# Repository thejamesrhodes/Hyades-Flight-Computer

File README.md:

---

# Hyades Flight Computer

Custom STM32H743 flight computer and GNC software for a roll-rate-stabilised high-power rocket.

*This is an engineering project, not a product. The safety case, regulatory compliance, and airworthiness of any vehicle built from this material are the builder's sole responsibility.*

The project is designed to:
- Provide a modular active roll-rate damping system suitable for a wide range of high-power rockets.
- Improve flight data quality by reducing excessive vehicle roll.
- Improve parachute deployment reliability by limiting roll-induced line twist.
- Provide a reusable avionics platform for future guidance, navigation and control research.
- Maintain compliance with applicable rocketry regulations through both hardware and software design decisions.
- Release all hardware, firmware and simulation tools as open source.

**Control scope.** The flight controller closes a loop on roll *rate*, not roll *angle*. It damps rate transients and cancels the standing roll moment produced by build asymmetry. It holds no commanded heading and has no outer attitude loop. Roll-angle hold and full three-axis attitude control are planned work and are not implemented.

This repository contains the hardware design, embedded software, simulation models, and analysis tools used during development.

---

## Specification

| Parameter | Specification |
|-----------|---------------|
| Purpose | Active roll stabilisation for mid- and high-power rockets |
| Flight Computer | STM32H743 ARM Cortex-M7 |
| Control Surfaces | Four independently actuated canards |
| Control System | Proportional roll-rate damper, dynamic-pressure gain scheduled, with a slow bounded trim path for bias rejection |
| Control Scope | Roll rate damping and bias rejection. No attitude loop |
| Interfaces | I²C, UART and 6× PWM outputs |
| Data | On-board logging with optional telemetry |
| Simulation | MATLAB, Simulink, 6DOF modelling and Monte Carlo analysis |
| Architecture | Modular flight computer, sensor board and power distribution board |
| Design Goals | Low mass, modular, reliable and adaptable |
| License | Apache 2.0 |

---

## Project Progress

| Feature                         | Status |
|---------------------------------|:------:|
| Flight Computer Design          | Complete |
| Flight Computer Testing         | In Progress |
| Flight Software                 | In Progress |
| Flight Hardware Design          | In Progress |
| Flight Hardware Testing         | In Progress |
| Simulink Roll Model             | Complete |
| Simulink 6DOF Model             | Complete |
| MATLAB Monte Carlo Analysis     | Complete |
| System Integration              | Not Started |
| HITL Testing                    | Not Started |
| Flight Testing                  | Not Started |

---

## Repository Structure

```text
Hyades-Flight-Computer
│
├── Documentation/
│   └── Images/
├── Firmware/
│   └── STM32IDE/
├── Hardware/
│   ├── 29mm Rocket/
│   ├── Avionics Bay/
│   ├── Canards/
│   ├── Fin Can/
│   └── PCB Designs/
└── Simulation/
    ├── Buck Regulator SPICE Simulation/
    ├── Canard Sizing/
    ├── HSE Clock SPICE Simulation/
    └── Matlab Roll Tuning/
```

---

## Flight Computer Design

The main PCB, containing all the computation and data gathering.

<p align="center"><i>Rev 0.2 render; rev 0.3 layout in progress.</i>
</p>

The PDB board, provides power and distributes PWM signals to the servos, as well as providing a clean 3V3 to the sensor board.

0 Ohm Series Termination vs 47 Ohm Series Termination for the 24 MHz HSE Oscillator, unnecessary? Yes, but a good opportunity to learn SPICE Simulations, plus it looks cool.
Below the schematic that the simulations were derived from.

---

## Flight Computer Testing

The second hardware iteration of the flight computer. The first failed due to many oversights and lack of basic knowledge.
On this version, the MCU boots and runs, USB and PDB works completely. An incorrectly wired CS pin has caused a bus fault where the I2C bus thinks its SPI and so fails to communicate. Future redesign to address this and a number of other design/architecture level issues is in progress, enabled by kind sponsorship from JLCPCB. Also seen is the Sheppard PCB design for my research project, which served a dual purpose in allowing me to validate the layout and connections for all the critical components for the next iteration, such as the ICM-42688P IMU and STM32H743 MCU and controlled impedance USB-HS routing for high data rate logging.

After some more testing, I have realised that the supposed ICM-42688-P's are actually QMI8658A IMU, substituted as a fake version of the target gyros (cross referenced WHO_AM_I 0x05, rev 0x7C, address 0x6B), after rewriting some of the code I got them working, allowing for a breakout board/bodge to be avoided. After collecting 2+ hours of data running at 16 g, 2048 dps, 224.2~ Hz ODR over I2C at 400kHz, I computed allan variance and then fitted a white-noise + Gauss-Markov + random-walk model to it (GMWM) with the rate-quantisation component computed separately under PQN model assumptions.

This is beneficial as the state estimator (IEKF) requires a model of the sensors noise to optimally estimate the current pose and to make its covariance trustworthy, which fault detection partly relies on. See [Quantisation Research Project](https://github.com/thejamesrhodes/IMU-Quantisation-research-project) for my related work on this topic.

---

## Flight Hardware Design

The built airframe, assembled and with the front avionics section separated from the booster.

CAD full assembly, an earlier render with the front section and nose cone missing.

Spinning Rear Fin Can designed to avoid the roll reversal phenomenon where upstream control surfaces tip vortices interact with the downstream fixed fins, causing a difficult to predict moment in the opposite direction.

Front avionics assembly, WIP.

---

## Flight Hardware Testing

%words

---

## Flight Software

%words

---

# Simulation

---

## Roll Control Architecture

The loop closes on roll rate, along two paths.

**Damping** is proportional and gain scheduled on dynamic pressure, `Kp = c / q_e`. The 1/q schedule holds the open-loop crossover constant across the envelope.

**Trim** is a slow bounded integrator that cancels the standing roll moment `Cl_0` from fin cant and build asymmetry. It is kept out of the damper because the deflection that cancels a standing bias, `-Cl_0 / Cl_delta`, is independent of q and V - one fixed deflection works everywhere, so it can be learned slowly and stay clear of the loop dynamics. Four gates bound it: bandwidth, a dead zone subtracted from the integrator input, a saturation freeze, and a clamp with a rate limit. It accepts an external `Cl_0` estimate, so a future MEKF can supply the value directly.

Putting integral action in the damper instead produces a limit cycle against the servo dead zone. That dead zone sits inside the servo's own position loop, so command-side compensation does not reach it; dither on the command does. Flown at 1.5x the modelled dead zone, 125 Hz.

**Open items.** The trim saturation gate tests the pre-dither command while the travel clamp acts post-dither, so it can miss a saturation event within one dither amplitude of the stop. The dither frequency also needs checking against the servo's maximum frame rate.

---

## Simulink Roll Model

%words

---

## Simulink 6DOF Model

%words

---

## MATLAB Monte Carlo Analysis

400 dispersed runs per design point. Aerodynamic coefficients, vehicle properties, actuator parameters and the disturbance bias are sampled per run. The controller's dynamic-pressure estimate is drawn about the sampled truth rather than the nominal, so scheduling error compounds with aerodynamic dispersion instead of cancelling against it.

| Metric | Definition |
|---|---|
| `rms_err` | RMS of (p - ref) over the steady tail |
| `bias` | mean(p) - ref over the tail |
| `ripple_pp` | max(p) - min(p) over the tail; limit-cycle amplitude |
| `activity` | RMS surface rate; catches stick-slip |
| `growth` | RMS of the last half of the tail over the first half; the stability test |
| `travel_peak` / `travel_steady` | Travel used over the whole run / over the tail |

Dither amplitude was swept over four campaigns at matched dispersion. Limit-cycle amplitude falls sharply at the flown setting with no rise in surface activity; the cost shows up as a small steady rate bias.

<!-- FIGURE SLOT A: settling-time and rate-error distributions, regenerated against
     the current canard geometry and the flown gainset. -->

<!-- FIGURE SLOT B: parameter-vs-outcome correlation structure, regenerated. -->

---

## MATLAB Gain Optimisation

`c` is set analytically from a 4 Hz crossover target; the numerical work confirms the margins near it survive parameter uncertainty rather than searching for an optimum. Margins come from the open-loop frequency response with the transport delay treated exactly, evaluated over paired (q, V) flight conditions spanning q = 2-40 kPa, with independent +/-30% on `Cl_delta` and `Cl_p`, accepted at phase margin >= 35 deg, gain margin >= 6 dB and peak sensitivity <= 2.0 at the worst corner. Constants are read from the parameter file rather than restated here.

A separate grid search over `c` and the trim parameters scores candidates on settling time, hang-off, limit-cycle amplitude and actuator demand, using the Monte Carlo campaign at each point.

`Ti` applies only to the legacy PI mode kept for A/B comparison.

<!-- FIGURE SLOT C: stability-margin and failure-probability maps over c, regenerated
     against the current canard. The previously published heatmaps are from the legacy
     PI controller and the earlier canard geometry. -->

---

## System Integration

%words

---

## HITL Testing

%words

---

## Flight Testing

%words

---

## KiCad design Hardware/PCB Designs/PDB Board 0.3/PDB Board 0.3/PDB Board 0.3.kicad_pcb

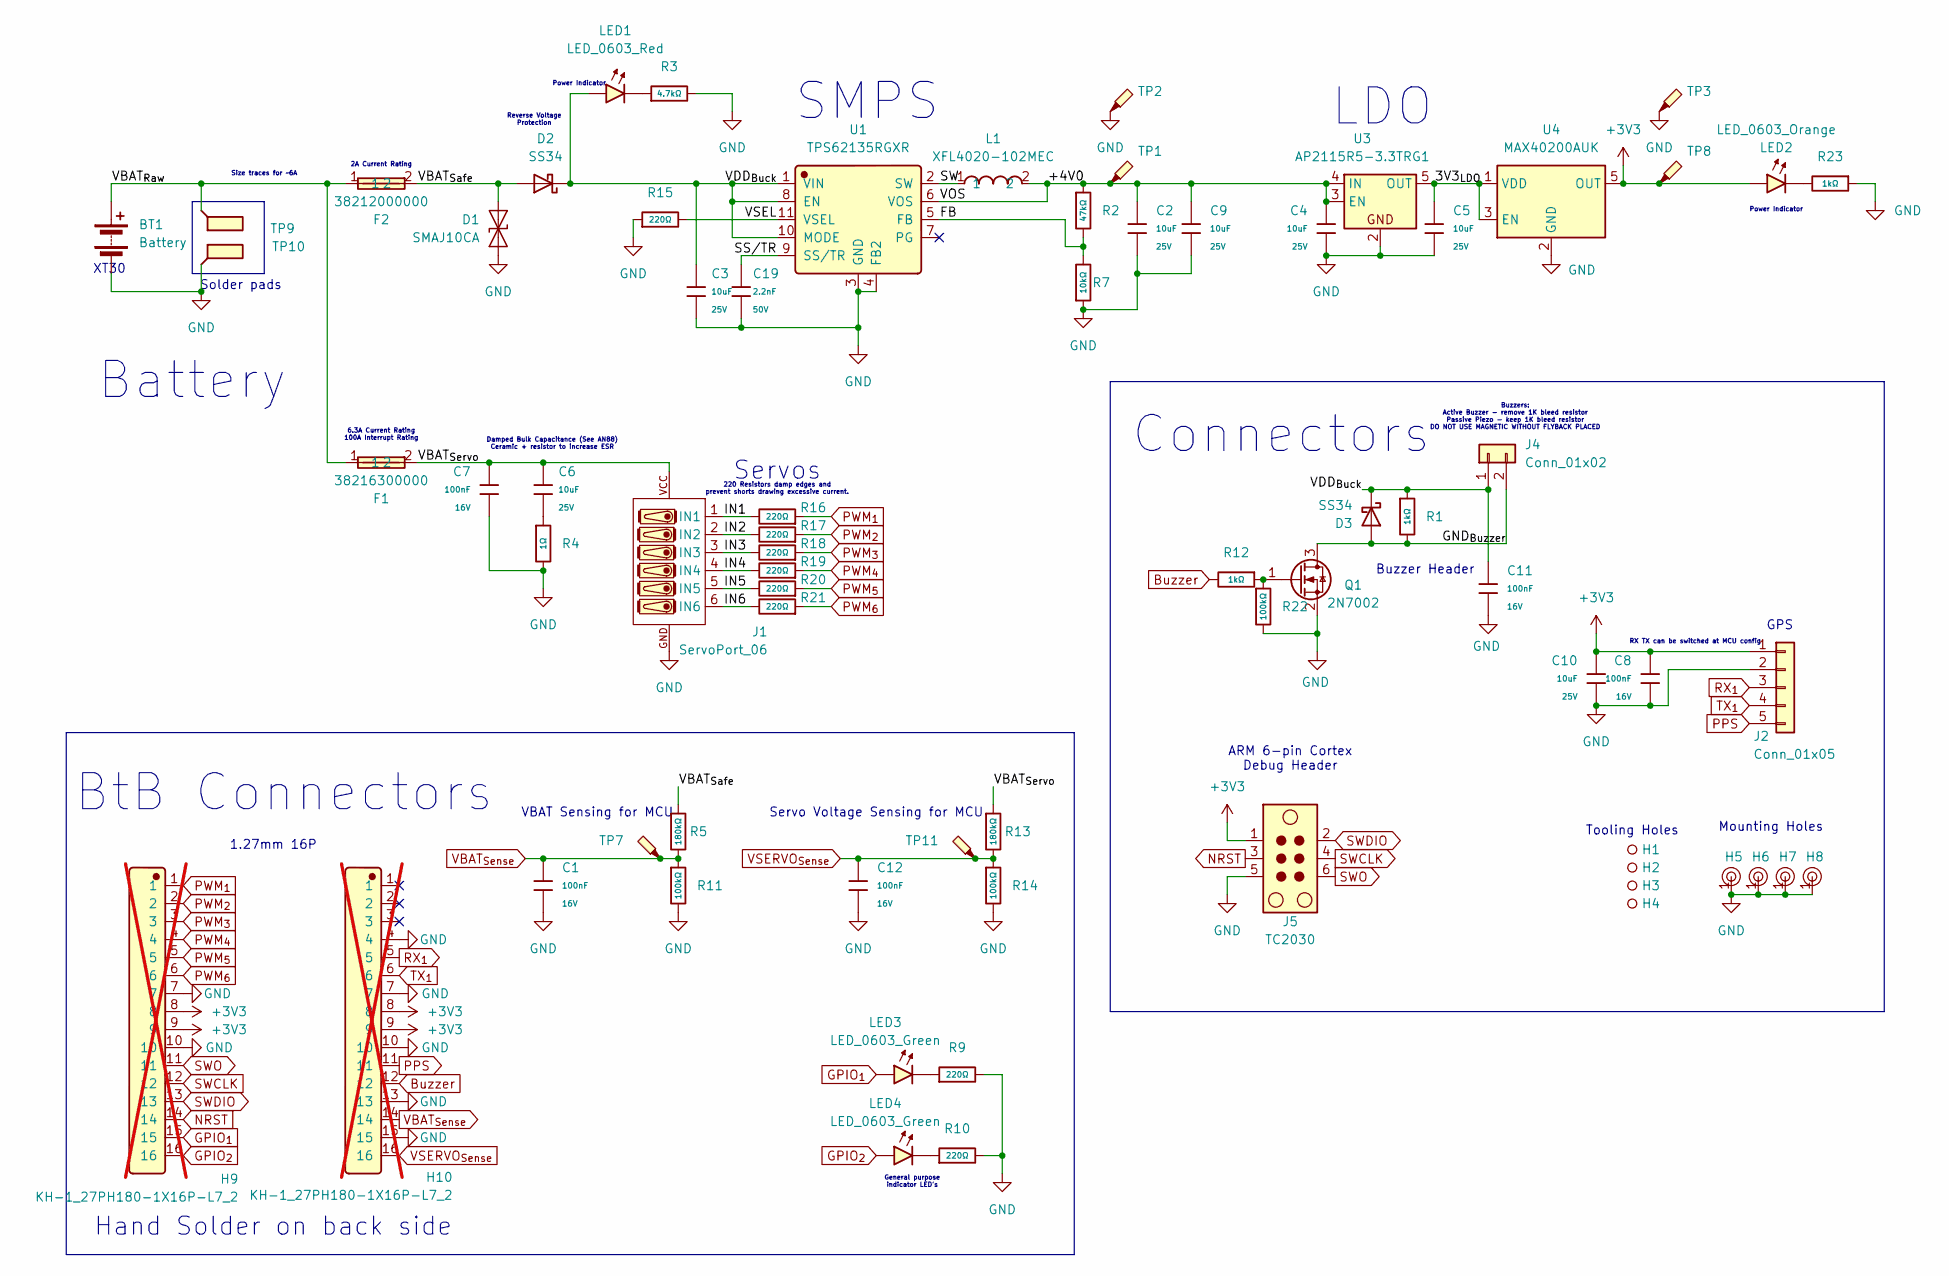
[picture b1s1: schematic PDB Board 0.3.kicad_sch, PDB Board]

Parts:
BT1: Battery; XT30UPB-M
C1, C7, C8, C11, C12: 100nF; C_0402; Voltage Rated 16V; Tolerance ±10%; Part CL05B104KO5NNNC; LCSC C1525
C2, C3, C4, C5, C6, C9, C10: 10uF; C_0805; Voltage Rated 25V; Tolerance ±10%; Part CL21A106KAYNNNE; LCSC C15850
C19: 2.2nF; C_0402; Voltage Rated 50V; Tolerance ±10%; Part 0402B222K500NT; LCSC C1531
D1: SMAJ10CA; D_SMA
D2, D3: SS34; D_SMA
F1: 38216300000; Manufacturer Part 38216300000; LCSC C142713
F2: 38212000000; Manufacturer Part 38212000000; LCSC C142740
H1, H2, H3, H4: Hole_Tooling_JLCPCB
H5, H6, H7, H8: Hole, 3mm
H9, H10: KH-1_27PH180-1X16P-L7_2; Manufacturer Part KH-1.27PH180-1X16P-L7.2; LCSC C2938407; not fitted
J1: ServoPort_06; ServoPort_06_Vertical
J2: Conn_01x05; JST_XH_B5B-XH-A_1x05_P2.50mm_Vertical
J4: Conn_01x02; JST_XH_B2B-XH-A_1x02_P2.50mm_Vertical; Part Number 1-0201FBV0T
J5: TC2030; Tag-Connect_TC2030-IDC-NL_2x03_P1.27mm_Vertical
L1: XFL4020-102MEC; Manufacturer Part XFL4020-102MEC; LCSC C5355380
LED1: LED_0603_Red; LED_0603_1608Metric
LED2: LED_0603_Orange; LED_0603_1608Metric
LED3, LED4: LED_0603_Green; LED_0603_1608Metric
Q1: 2N7002; SOT-23
R1, R12, R23: 1kΩ; R_0805; Overload Voltage (Max) 150V; Tolerance ±1%; Part 0805W8F1001T5E; LCSC C17513
R2: 47kΩ; R_0603; Overload Voltage (Max) 75V; Tolerance ±1%; Part 0603WAF4702T5E; LCSC C25819
R3: 4.7kΩ; R_0603; Overload Voltage (Max) 75V; Tolerance ±1%; Part 0603WAF4701T5E; LCSC C23162
R4: 1Ω; R_0805; Overload Voltage (Max) 150V; Tolerance ±1%; Part 0805W8F100KT5E; LCSC C25271
R5, R13: 180kΩ; R_0603; Overload Voltage (Max) 75V; Tolerance ±1%; Part 0603WAF1803T5E; LCSC C22827
R7: 10kΩ; R_0402; Overload Voltage (Max) 50V; Tolerance ±1%; Part 0402WGF1002TCE; LCSC C25744
R9, R10, R15, R16, R17, R18, R19, R20, R21: 220Ω; R_0402; Overload Voltage (Max) 50V; Tolerance ±1%; Part 0402WGF2200TCE; LCSC C25091
R11, R14, R22: 100kΩ; R_0402; Overload Voltage (Max) 50V; Tolerance ±1%; Part 0402WGF1003TCE; LCSC C25741
TP1, TP2, TP3, TP7, TP8, TP11: TestPoint_Probe; TestPoint_Pad_04
TP9, TP10: TestPoint_Flag; SolderWirePad_1x01_SMD_4x8mm
U1: TPS62135RGXR; Manufacturer Part TPS62135RGXR; LCSC C167238
U3: AP2115R5-3.3TRG1; Diodes_SOT-89-5; LCSC C460316
U4: MAX40200AUK; SOT-23-5

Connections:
+3V3: C8.1, C10.1, H9.8, H9.9, H10.8, H10.9, J2.1, J5.1, LED2.2 (A), TP8.1 (1_1), U4.5 (OUT)
/3V3_{LDO}: C5.1, U3.5 (OUT), U4.1 (VDD), U4.3 (EN)
/+4V0: C2.1, C4.1, C9.1, L1.2, R2.1, TP1.1 (1_1), U1.6 (VOS), U3.3 (EN), U3.4 (IN)
/FB: R2.2, R7.2, U1.5 (FB)
/GND_{Buzzer}: D3.2 (A), J4.2, Q1.3 (D), R1.2
/IN1: J1.1 (IN1), R16.2
/IN2: J1.2 (IN2), R17.2
/IN3: J1.3 (IN3), R18.2
/IN4: J1.4 (IN4), R19.2
/IN5: J1.5 (IN5), R20.2
/IN6: J1.6 (IN6), R21.2
/SS/TR: C19.1, U1.9 (SS/TR)
/SW: L1.1, U1.2 (SW)
/VBAT_{Raw}: BT1.1 (+), F1.1, F2.1, TP9.1 (1_1)
/VBAT_{Safe}: D1.2 (A2), D2.2 (A), F2.2, R5.1
/VBAT_{Servo}: C6.1, C7.1, F1.2, J1.VCC, R13.1
/VDD_{Buck}: C3.1, C11.1, D2.1 (K), D3.1 (K), J4.1, LED1.2 (A), R1.1, U1.1 (VIN), U1.8 (EN), U1.10 (MODE)
/VSEL: R15.2, U1.11 (VSEL)
Buzzer: H10.12, R12.2
GND: BT1.2 (-), C1.2, C2.2, C3.2, C4.2, C5.2, C7.2, C8.2, C9.2, C10.2, C11.2, C12.2, C19.2, D1.1 (A1), H5.1, H6.1, H7.1, H8.1, H9.7, H9.10, H10.4, H10.7, H10.10, H10.13, H10.15, J1.GND, J2.2, J5.5, Q1.2 (S), R3.2, R4.2, R7.1, R9.2, R10.2, R11.2, R14.2, R15.1, R22.2, R23.1, TP2.1 (1_1), TP3.1 (1_1), TP10.1 (1_1), U1.3 (GND), U1.4 (FB2), U3.2, U4.2 (GND)
GPIO_{1}: H9.15, LED3.2 (A)
GPIO_{2}: H9.16, LED4.2 (A)
NRST: H9.14, J5.3
unnamed: C6.2, R4.1
unnamed: LED1.1 (K), R3.1
unnamed: LED2.1 (K), R23.2
unnamed: LED3.1 (K), R9.1
unnamed: LED4.1 (K), R10.1
unnamed: Q1.1 (G), R12.1, R22.1
PPS: H10.11, J2.5
PWM_{1}: H9.1, R16.1
PWM_{2}: H9.2, R17.1
PWM_{3}: H9.3, R18.1
PWM_{4}: H9.4, R19.1
PWM_{5}: H9.5, R20.1
PWM_{6}: H9.6, R21.1
RX_{1}: H10.5, J2.3
SWCLK: H9.12, J5.4
SWDIO: H9.13, J5.2
SWO: H9.11, J5.6
TX_{1}: H10.6, J2.4
VBAT_{Sense}: C1.1, H10.14, R5.2, R11.1, TP7.1 (1_1)
VSERVO_{Sense}: C12.1, H10.16, R13.2, R14.1, TP11.1 (1_1)

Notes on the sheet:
Power Indicator
SMPS
Solder pads
2A Current Rating
Buzzer Header
Servos
BtB Connectors
220 Resistors damp edges and prevent shorts drawing excessive current.
Connectors
Buzzers: Active Buzzer - remove 1K bleed resistor Passive Piezo - keep 1K bleed resistor DO NOT USE MAGNETIC WITHOUT FLYBACK PLACED
Reverse Voltage Protection
GPS
General purpose indicator LED's
Servo Voltage Sensing for MCU
1.27mm 16P
Mounting Holes
LDO
6.3A Current Rating 100A Interrupt Rating
Battery
RX TX can be switched at MCU config
XT30
Damped Bulk Capacitance (See AN88) Ceramic + resistor to increase ESR
ARM 6-pin Cortex Debug Header
VBAT Sensing for MCU
Hand Solder on back side
Size traces for ~6A
Tooling Holes

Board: 4 copper layers, 71 parts (2 on the bottom side), 43 nets, no tracks yet.
